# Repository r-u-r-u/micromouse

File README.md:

# マイクロマウス関連の事をまとめるリポジトリ

pass:rurumouse  
[今の機体](https://a360.co/3c0cTEl)  

[競技規定](https://www.ntf.or.jp/mouse/micromouse2013/kitei_classic_since2013.html)

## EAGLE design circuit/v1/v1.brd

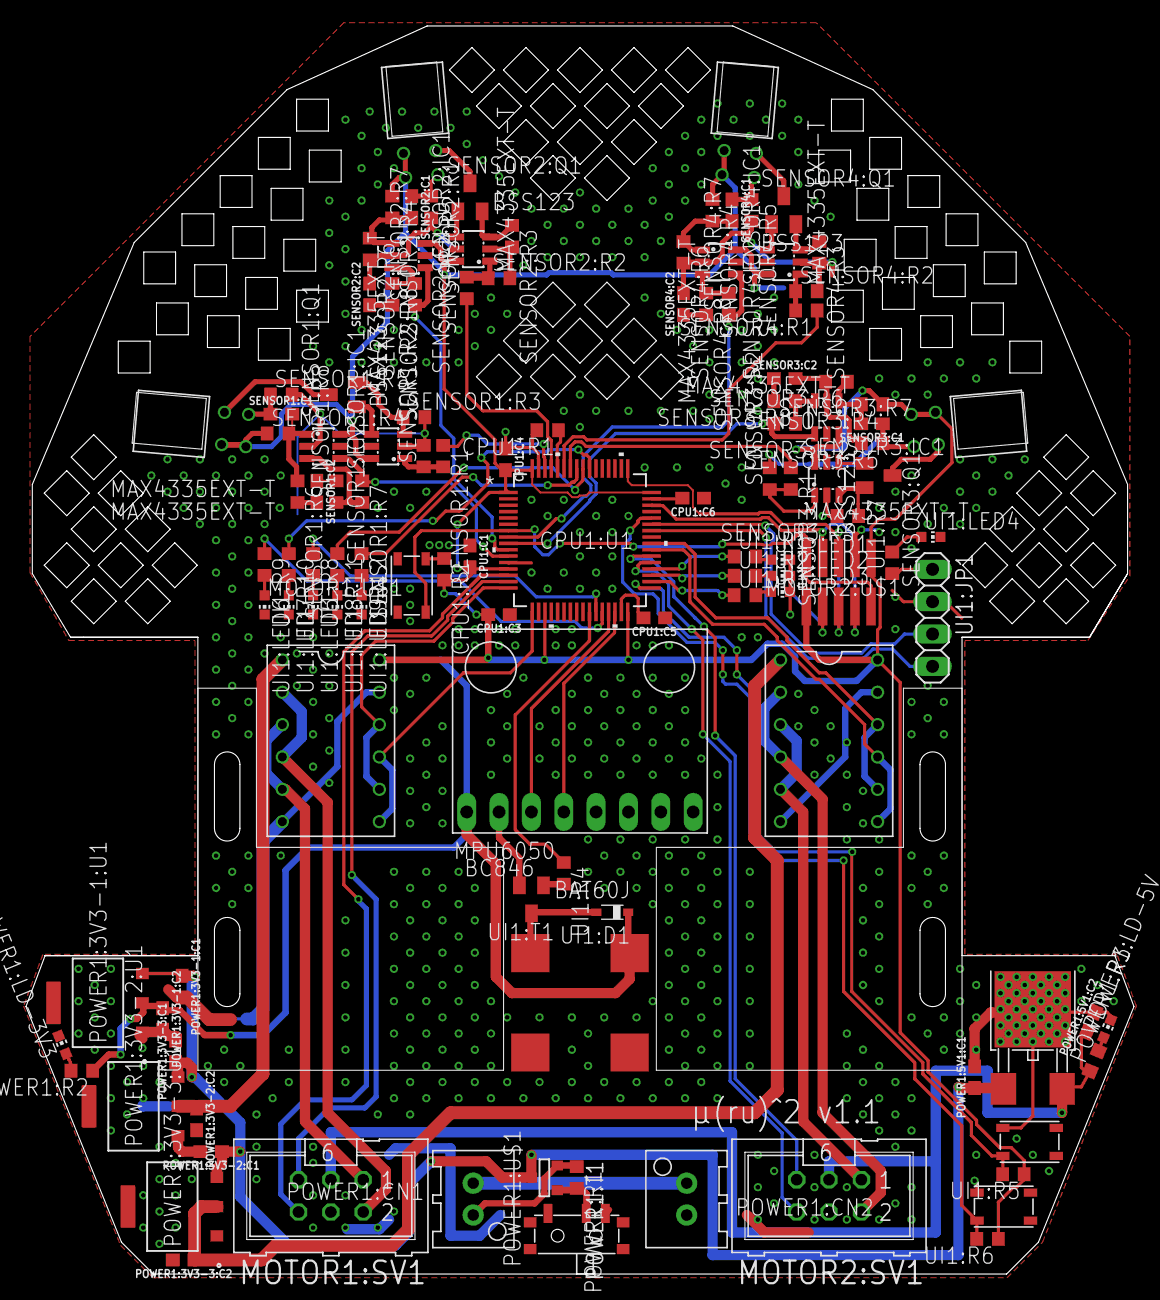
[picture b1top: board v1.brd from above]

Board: 2 copper layers, 87.0 x 98.0 mm, 119 parts (0 on the bottom side), 97 nets.

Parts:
CPU1:C1, CPU1:C3, CPU1:C4, CPU1:C5, CPU1:C6: 0.1uF; 0603
CPU1:R1: 10k; R0603
CPU1:R2: R0603
CPU1:U1: STM32F405RGT6; LQFP-64
CPU1:U$1: SKRPACE010
CPU1:U$2: PINHEAD_10_127; PINHEAD
GYRO1:U$1: MPU-6050-BOARD; BOARD
MOTOR1:SV1, MOTOR2:SV1: ML6
MOTOR1:U$1, MOTOR2:U$1: AE-DRV8835; DIP_12
POWER1:3V3-1:C1, POWER1:3V3-1:C2, POWER1:3V3-2:C1, POWER1:3V3-2:C2, POWER1:3V3-3:C1, POWER1:3V3-3:C2, POWER1:5V1:C1, POWER1:5V1:C2: 10nF; 0603
POWER1:3V3-1:U1, POWER1:3V3-2:U1, POWER1:3V3-3:U1: AZ1086H-3.3; SOT-223_ST
POWER1:5V1:U$1: NJM7805; TO-252-3
POWER1:CN1, POWER1:CN2: 2PIN-TOP; B02B-XASK-N
POWER1:LD-3V3, POWER1:LD-5V: CHIP-LED0603
POWER1:R1, POWER1:R2, POWER1:R3: R0603
POWER1:T1: SOT-23
POWER1:U$1: SSW1P2T
SENSOR1:C1, SENSOR1:C2, SENSOR2:C1, SENSOR2:C2, SENSOR3:C1, SENSOR3:C2, SENSOR4:C1, SENSOR4:C2: 0.1uF; 0603
SENSOR1:IC1, SENSOR1:IC2, SENSOR2:IC1, SENSOR2:IC2, SENSOR3:IC1, SENSOR3:IC2, SENSOR4:IC1, SENSOR4:IC2: MAX4335EXT-T; SOT23-6L
SENSOR1:Q1, SENSOR2:Q1, SENSOR3:Q1, SENSOR4:Q1: BSS123; SOT23
SENSOR1:R1, SENSOR1:R2, SENSOR2:R1, SENSOR2:R2, SENSOR3:R1, SENSOR3:R2, SENSOR4:R1, SENSOR4:R2: R0603
SENSOR1:R3, SENSOR2:R3, SENSOR3:R3, SENSOR4:R3: 47; R0603
SENSOR1:R4, SENSOR1:R7, SENSOR2:R4, SENSOR2:R7, SENSOR3:R4, SENSOR3:R7, SENSOR4:R4, SENSOR4:R7: 100k; R0603
SENSOR1:R5, SENSOR2:R5, SENSOR3:R5, SENSOR4:R5: 1k; R0603
SENSOR1:R6, SENSOR1:R8, SENSOR2:R6, SENSOR2:R8, SENSOR3:R6, SENSOR3:R8, SENSOR4:R6, SENSOR4:R8: 10k; R0603
SENSOR1:U$1, SENSOR2:U$1, SENSOR3:U$1, SENSOR4:U$1: LBR-127HLD
UI1:D1: BAT60J; SOD323_ST
UI1:JP1: 1X04
UI1:LED1, UI1:LED2, UI1:LED3, UI1:LED4, UI1:LED5, UI1:LED6, UI1:LED7, UI1:LED8, UI1:LED9: CHIP-LED0603
UI1:R1, UI1:R2, UI1:R3, UI1:R4, UI1:R5, UI1:R6, UI1:R7, UI1:R8, UI1:R9, UI1:R10, UI1:R11, UI1:R12: R0603
UI1:T1: BC846; SOT23
UI1:U$1: UGCT725AN4; UGCT7525AN4
UI1:U$2, UI1:U$3: SKRPACE010

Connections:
3V3: CPU1:C1.2, CPU1:C3.2, CPU1:C4.2, CPU1:R2.2, CPU1:U1.1, CPU1:U1.13, CPU1:U1.19, CPU1:U1.32, CPU1:U1.48, CPU1:U1.64, CPU1:U$2.1, CPU1:U$2.6, GYRO1:U$1.VCC, MOTOR1:U$1.12, MOTOR2:U$1.12, POWER1:3V3-1:C2.1, POWER1:3V3-1:U1.2, POWER1:R2.1, SENSOR1:IC1.6, SENSOR1:IC2.6, SENSOR1:R4.1, SENSOR1:U$1.P$1, SENSOR1:U$1.P$3, SENSOR2:IC1.6, SENSOR2:IC2.6, SENSOR2:R4.1, SENSOR2:U$1.P$1, SENSOR2:U$1.P$3, SENSOR3:IC1.6, SENSOR3:IC2.6, SENSOR3:R4.1, SENSOR3:U$1.P$1, SENSOR3:U$1.P$3, SENSOR4:IC1.6, SENSOR4:IC2.6, SENSOR4:R4.1, SENSOR4:U$1.P$1, SENSOR4:U$1.P$3, UI1:D1.C, UI1:R5.1, UI1:R6.1, UI1:U$1.+
5V: MOTOR1:SV1.3, MOTOR2:SV1.3, POWER1:5V1:C2.1, POWER1:5V1:U$1.3, POWER1:R3.1
CPU1:N$1: CPU1:R1.1, CPU1:U1.60
CPU1:N$2: CPU1:R2.1, CPU1:U$1.1
CPU1:N$3: CPU1:C5.2, CPU1:U1.31
CPU1:N$4: CPU1:C6.2, CPU1:U1.47
CPU1:NRST: CPU1:U1.7, CPU1:U$1.2, CPU1:U$2.5, CPU1:U$2.10
CPU1:SWCLK: CPU1:U1.49, CPU1:U$2.3, CPU1:U$2.8
CPU1:SWDIO: CPU1:U1.46, CPU1:U$2.4, CPU1:U$2.9
GND: CPU1:C1.1, CPU1:C3.1, CPU1:C4.1, CPU1:C5.1, CPU1:C6.1, CPU1:R1.2, CPU1:U1.12, CPU1:U1.18, CPU1:U1.63, CPU1:U$1.4, CPU1:U$2.2, CPU1:U$2.7, GYRO1:U$1.GND, MOTOR1:SV1.4, MOTOR1:U$1.6, MOTOR1:U$1.11, MOTOR2:SV1.4, MOTOR2:U$1.6, MOTOR2:U$1.11, POWER1:3V3-1:C1.2, POWER1:3V3-1:C2.2, POWER1:3V3-1:U1.1, POWER1:3V3-2:C1.2, POWER1:3V3-2:C2.2, POWER1:3V3-2:U1.1, POWER1:3V3-3:C1.2, POWER1:3V3-3:C2.2, POWER1:3V3-3:U1.1, POWER1:5V1:C1.2, POWER1:5V1:C2.2, POWER1:5V1:U$1.2, POWER1:CN2.P$2, POWER1:LD-3V3.C, POWER1:LD-5V.C, POWER1:U$1.C, SENSOR1:C2.2, SENSOR1:IC1.2, SENSOR1:IC2.2, SENSOR1:R2.2, SENSOR1:R3.2, SENSOR1:R5.2, SENSOR1:R6.2, SENSOR2:C2.2, SENSOR2:IC1.2, SENSOR2:IC2.2, SENSOR2:R2.2, SENSOR2:R3.2, SENSOR2:R5.2, SENSOR2:R6.2, SENSOR3:C2.2, SENSOR3:IC1.2, SENSOR3:IC2.2, SENSOR3:R2.2, SENSOR3:R3.2, SENSOR3:R5.2, SENSOR3:R6.2, SENSOR4:C2.2, SENSOR4:IC1.2, SENSOR4:IC2.2, SENSOR4:R2.2, SENSOR4:R3.2, SENSOR4:R5.2, SENSOR4:R6.2, UI1:JP1.2, UI1:LED1.C, UI1:LED2.C, UI1:LED3.C, UI1:LED4.C, UI1:LED5.C, UI1:LED6.C, UI1:LED7.C, UI1:LED8.C, UI1:LED9.C, UI1:T1.2, UI1:U$2.4, UI1:U$3.4
MOTOR1:M+: MOTOR1:SV1.2, MOTOR1:U$1.2, MOTOR1:U$1.4
MOTOR1:M-: MOTOR1:SV1.1, MOTOR1:U$1.3, MOTOR1:U$1.5
MOTOR2:M+: MOTOR2:SV1.2, MOTOR2:U$1.2, MOTOR2:U$1.4
MOTOR2:M-: MOTOR2:SV1.1, MOTOR2:U$1.3, MOTOR2:U$1.5
unnamed: CPU1:U1.38, MOTOR2:SV1.5
unnamed: CPU1:U1.37, MOTOR2:SV1.6
unnamed: CPU1:U1.39, MOTOR2:U$1.7, MOTOR2:U$1.9
unnamed: CPU1:U1.15, MOTOR1:SV1.5
unnamed: CPU1:U1.40, MOTOR2:U$1.8, MOTOR2:U$1.10
unnamed: CPU1:U1.14, MOTOR1:SV1.6
unnamed: CPU1:U1.17, MOTOR1:U$1.7, MOTOR1:U$1.9
unnamed: CPU1:U1.16, MOTOR1:U$1.8, MOTOR1:U$1.10
unnamed: CPU1:U1.36, UI1:R1.1
unnamed: CPU1:U1.35, UI1:R2.1
unnamed: CPU1:U1.34, UI1:R3.1
unnamed: CPU1:U1.26, UI1:R4.1
unnamed: CPU1:U1.33, UI1:R5.2, UI1:U$2.2
unnamed: CPU1:U1.44, UI1:R6.2, UI1:U$3.2
unnamed: CPU1:U1.30, GYRO1:U$1.SDA
unnamed: CPU1:U1.29, GYRO1:U$1.SCL
unnamed: CPU1:U1.62, SENSOR1:R1.1
unnamed: CPU1:U1.61, SENSOR2:R1.1
unnamed: CPU1:U1.11, SENSOR1:IC2.4, SENSOR1:R7.1
unnamed: CPU1:U1.10, SENSOR2:IC2.4, SENSOR2:R7.1
unnamed: CPU1:U1.58, SENSOR3:R1.1
unnamed: CPU1:U1.9, SENSOR3:IC2.4, SENSOR3:R7.1
unnamed: CPU1:U1.59, SENSOR4:R1.1
unnamed: CPU1:U1.8, SENSOR4:IC2.4, SENSOR4:R7.1
unnamed: CPU1:U1.42, UI1:JP1.4
unnamed: CPU1:U1.43, UI1:JP1.3
unnamed: CPU1:U1.27, UI1:R8.1
unnamed: CPU1:U1.28, UI1:R9.1
unnamed: CPU1:U1.55, UI1:R10.1
unnamed: CPU1:U1.56, UI1:R11.1
unnamed: CPU1:U1.57, UI1:R12.1
POWER1:BAT: POWER1:CN1.P$1, POWER1:R1.1, POWER1:T1.2
POWER1:N$1: POWER1:R1.2, POWER1:T1.3, POWER1:U$1.B
POWER1:N$2: POWER1:CN1.P$2, POWER1:CN2.P$1
POWER1:N$3: POWER1:LD-3V3.A, POWER1:R2.2
POWER1:N$4: POWER1:LD-5V.A, POWER1:R3.2
POWER1:VCC: POWER1:3V3-1:C1.1, POWER1:3V3-1:U1.3, POWER1:3V3-2:C1.1, POWER1:3V3-2:U1.3, POWER1:3V3-3:C1.1, POWER1:3V3-3:U1.3, POWER1:5V1:C1.1, POWER1:5V1:U$1.1, POWER1:T1.1
SENSOR1:N$1: SENSOR1:IC1.1, SENSOR1:R1.2, SENSOR1:R2.1
SENSOR1:N$2: SENSOR1:IC1.3, SENSOR1:Q1.2, SENSOR1:R3.1
SENSOR1:N$3: SENSOR1:IC1.4, SENSOR1:Q1.1
SENSOR1:N$4: SENSOR1:C1.2, SENSOR1:IC2.1, SENSOR1:R4.2, SENSOR1:R6.1
SENSOR1:N$5: SENSOR1:Q1.3, SENSOR1:U$1.P$2
SENSOR1:N$7: SENSOR1:IC2.3, SENSOR1:R7.2, SENSOR1:R8.1
SENSOR1:N$8: SENSOR1:C2.1, SENSOR1:R8.2
SENSOR1:N$9: SENSOR1:C1.1, SENSOR1:R5.1, SENSOR1:U$1.P$4
SENSOR2:N$1: SENSOR2:IC1.1, SENSOR2:R1.2, SENSOR2:R2.1
SENSOR2:N$2: SENSOR2:IC1.3, SENSOR2:Q1.2, SENSOR2:R3.1
SENSOR2:N$3: SENSOR2:IC1.4, SENSOR2:Q1.1
SENSOR2:N$4: SENSOR2:C1.2, SENSOR2:IC2.1, SENSOR2:R4.2, SENSOR2:R6.1
SENSOR2:N$5: SENSOR2:Q1.3, SENSOR2:U$1.P$2
SENSOR2:N$7: SENSOR2:IC2.3, SENSOR2:R7.2, SENSOR2:R8.1
SENSOR2:N$8: SENSOR2:C2.1, SENSOR2:R8.2
SENSOR2:N$9: SENSOR2:C1.1, SENSOR2:R5.1, SENSOR2:U$1.P$4
SENSOR3:N$1: SENSOR3:IC1.1, SENSOR3:R1.2, SENSOR3:R2.1
SENSOR3:N$2: SENSOR3:IC1.3, SENSOR3:Q1.2, SENSOR3:R3.1
SENSOR3:N$3: SENSOR3:IC1.4, SENSOR3:Q1.1
SENSOR3:N$4: SENSOR3:C1.2, SENSOR3:IC2.1, SENSOR3:R4.2, SENSOR3:R6.1
SENSOR3:N$5: SENSOR3:Q1.3, SENSOR3:U$1.P$2
SENSOR3:N$7: SENSOR3:IC2.3, SENSOR3:R7.2, SENSOR3:R8.1
SENSOR3:N$8: SENSOR3:C2.1, SENSOR3:R8.2
SENSOR3:N$9: SENSOR3:C1.1, SENSOR3:R5.1, SENSOR3:U$1.P$4
SENSOR4:N$1: SENSOR4:IC1.1, SENSOR4:R1.2, SENSOR4:R2.1
SENSOR4:N$2: SENSOR4:IC1.3, SENSOR4:Q1.2, SENSOR4:R3.1
SENSOR4:N$3: SENSOR4:IC1.4, SENSOR4:Q1.1
SENSOR4:N$4: SENSOR4:C1.2, SENSOR4:IC2.1, SENSOR4:R4.2, SENSOR4:R6.1
SENSOR4:N$5: SENSOR4:Q1.3, SENSOR4:U$1.P$2
SENSOR4:N$7: SENSOR4:IC2.3, SENSOR4:R7.2, SENSOR4:R8.1
SENSOR4:N$8: SENSOR4:C2.1, SENSOR4:R8.2
SENSOR4:N$9: SENSOR4:C1.1, SENSOR4:R5.1, SENSOR4:U$1.P$4
UI1:N$1: UI1:LED1.A, UI1:R1.2
UI1:N$2: UI1:LED2.A, UI1:R2.2
UI1:N$3: UI1:LED3.A, UI1:R3.2
UI1:N$4: UI1:D1.A, UI1:T1.3, UI1:U$1.-
UI1:N$5: UI1:R4.2, UI1:T1.1
UI1:N$6: UI1:JP1.1, UI1:R7.1
UI1:N$7: UI1:LED4.A, UI1:R7.2
UI1:N$8: UI1:LED5.A, UI1:R8.2
UI1:N$9: UI1:LED6.A, UI1:R9.2
UI1:N$10: UI1:LED7.A, UI1:R10.2
UI1:N$11: UI1:LED8.A, UI1:R11.2
UI1:N$12: UI1:LED9.A, UI1:R12.2
VCCM1: MOTOR1:U$1.1, POWER1:3V3-2:C2.1, POWER1:3V3-2:U1.2
VCCM2: MOTOR2:U$1.1, POWER1:3V3-3:C2.1, POWER1:3V3-3:U1.2

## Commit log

2020-02-10 add readme
2020-02-10 add maze image file
2020-02-10 add circuit
2020-02-10 add program

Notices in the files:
parts and their libraries:
SparkFun-Capacitors: Licensing: Creative Commons ShareAlike 4.0 International - https://creativecommons.org/licenses/by-sa/4.0
